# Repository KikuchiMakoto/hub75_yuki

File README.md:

# HUB75 LED Matrix Controller System

128x32 HUB75 LEDマトリックスパネルを制御する完全なシステムです。RP2040 (Raspberry Pi Pico) とPythonアプリケーションで構成されています。

## プロジェクト構成

このプロジェクトは、**Application (Python)**、**Firmware**、**KiCad PCB** の3つのコンポーネントで構成されています：

```
├── application/       # Python制御アプリケーション (PC側)
│   └── src/           # LED Matrix Controller (画像/動画/カメラ/テキスト表示)
├── firmware/          # RP2040ファームウェア (Arduino core + PIO、COBSバイナリ通信)
│   └── src/           # HUB75ドライバ (PlatformIO/Arduino)
└── kicad_pcb/         # KiCad設計データ (基板レイアウト/ライブラリ)
```

### 役割分担

- **Firmware** (`firmware/`): RP2040上で動作するC++コード。HUB75パネルの駆動、PIO/DMAによる高速出力、USB CDCによるCOBSデータ受信、RGB565からBCM変換を担当。
- **Application (Python)** (`application/`): PC上で動作するPythonコード。画像/動画読み込み、リサイズ、RGB565変換、COBSエンコード、シリアル通信を担当。
- **KiCad PCB** (`kicad_pcb/`): 回路図シンボル/フットプリント/基板レイアウトなどのハードウェア設計データを管理。

### 通信プロトコル（絶対的ルール）

すべてのファームウェア・クライアント間で、以下のプロトコルは**絶対的な不変条件**です：

- **インターフェース**: USB CDC ACM
- **ペイロード形式**: RGB565 リトルエンディアン
- **エンコーディング**: COBS (Consistent Overhead Byte Stuffing)
- **フレーム区切り**: 末尾 `0x00`
- **総画素数 / ペイロード長**: **4,096 画素（8,192 バイト）**

### 動作モードとパネル配置（64x32 パネル 2枚構成）

本システムは、64x32 HUB75 パネル 2枚の物理配置と用途に応じて、以下の **2つの公式動作モード** を備えています：

1. **NormalMode (128x32)**:
   - **配置**: 64×32 パネルを左右に連結（横長バナー配置 / デフォルト）
   - **動作**: PC 上の Python コントローラー（`application/`）から USB CDC 経由で COBS 符号化 RGB565 フレームを受信し、Core1 が高速リフレッシュ駆動。動画、画像、テキスト、時計、デモアニメーションの再生に対応。
2. **StandaloneMode (64x64)**:
   - **配置**: 64×32 パネルを上下に積層（正方形 64×64 配置。下段の2枚目パネルはリボン配線に合わせて **180度回転マッピング** されます）
   - **動作**: PC 不要の完全スタンドアローン動作。RP2040 Core0（250MHz）が ADXL335 加速度センサ（`GP26` X / `GP27` Y）を読み取り、純粋な `float` (f32) 2D-DEM 珪砂シミュレーション（Spatial Grid 近傍探索 $O(N)$ により 30+ FPS）をリアルタイム計算。Core1 が 64×64 パネルを駆動する「電子珪砂時計 / 回転ドラム」モード。起動時の突入電流を抑える省電力ブート（即時ブラックアウト）を搭載。

> **更新レート（FPS）について**: これは**緩いルール**です。目標FPSはファームウェアの実装・最適化状況次第で変化します。クライアント側はできる限りのレートで送信し、ファームウェア側が受信・描画可能なタイミングで処理します。プロトコル形式（RGB565+COBS+0x00）を守ることが最優先です。

## 特徴

- **高速・安定表示**: PIO (7.14 MHz 最適化) + DMA による高速シフト出力（内部リフレッシュレート約 350 Hz、フリッカーフリー）
- **デュアルコア設計**: Core0 で USB 受信／DEM 物理演算＋BCM 変換、Core1 で 100% パネル駆動専任（完全チラつき防止）
- **ハードウェア除算アクセラレーション**: RP2040 SIO 32-bit 除算器による DEM 物理演算の高速化（約 250 FPS）
- **過大評価描画**: 2x2 box pixel の隙間・角抜けを排除した高密度・高輝度砂粒表示
- **即時起動**: 余計な起動スプラッシュやセルフテスト待ちを全廃し、電源投入直後から即時動作
- **RGB565フォーマット**: 16ビットカラー（5-6-5ビット）による効率的な転送
- **COBSエンコーディング**: 0x00区切りのバイナリフレーム転送
- **高画質**: 6ビットBCM（64階調）+ Gamma補正（2.2）
- **最新コードベース**: 不要な低速 CPU GPIO 駆動コードを全廃し、PIO + DMA 専用に一本化

## クイックスタート

### 必要なツール

- **Firmware用**: [PlatformIO](https://platformio.org/) - RP2040へのファームウェア書き込み
- **Application (Python) 用**: [uv](https://docs.astral.sh/uv/) - Pythonパッケージマネージャー

### セットアップ手順

#### 1. Firmwareをビルド・書き込み (初回のみ)

```bash
cd firmware
pio run -t upload
```

RP2040にファームウェアが書き込まれ、HUB75パネルの駆動が可能になります。

#### 2. Application (Python) を実行 (PC側)

uvをインストール:
```bash
# macOS / Linux
curl -LsSf https://astral.sh/uv/install.sh | sh

# Windows (PowerShell)
powershell -ExecutionPolicy ByPass -c "irm https://astral.sh/uv/install.ps1 | iex"
```

アプリケーションを実行:
```bash
cd application

# デモアニメーション
uv run led-matrix --demo rainbow

# 画像表示
uv run led-matrix --image sample.png

# 2D-DEM 珪砂シミュレーション (Taichi GPU, f32)
uv run led-matrix --dem

# 2D-DEM 64x64 Pixel/Voxel マトリクス表示
uv run led-matrix --dem-matrix

# ヘルプ表示
uv run led-matrix --help
```

詳細は各ディレクトリのREADMEを参照してください:
- [Application (Python) README](application/README.md)
- [Firmware README](firmware/README.md)
- [KiCad PCB データ](kicad_pcb/)

## ハードウェア要件

- Raspberry Pi Pico (RP2040)
- HUB75 LED パネル 64x32 x 2枚
- 3軸加速度センサ ADXL335 (3.3V電源)
  - **X軸**: `GP26` (ADC0)
  - **Y軸**: `GP27` (ADC1)
  - **Z軸**: 未使用（2D DEMのため不要）
  - **VCC**: `3V3` (3.3V)
  - **GND**: `GND`
- USBケーブル
- 5V電源 (LEDパネル用)

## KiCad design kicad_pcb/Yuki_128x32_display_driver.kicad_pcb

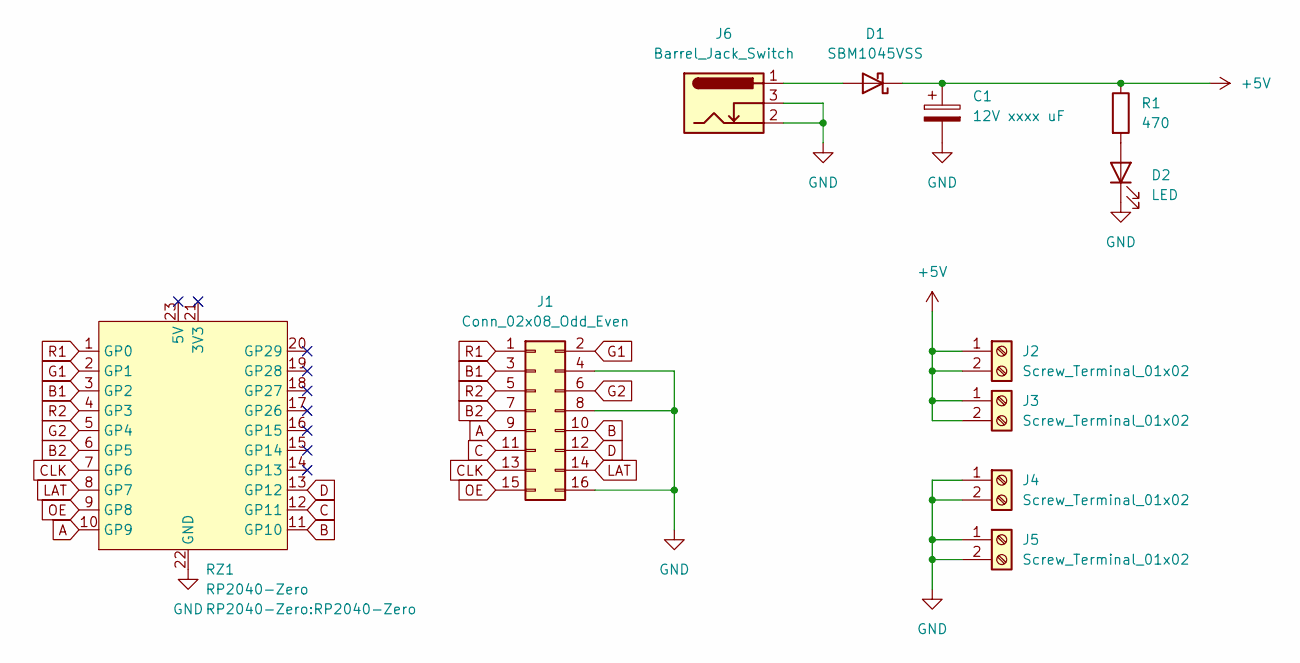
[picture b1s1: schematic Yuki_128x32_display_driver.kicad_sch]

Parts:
C1: 12V xxxx uF; CP_Radial_D13.0mm_P5.00mm
D1: SBM1045VSS; D_DO-201AD_P12.70mm_Horizontal
D2: LED; LED_D5.0mm
J1: Conn_02x08_Odd_Even; IDC-Header_2x08_P2.54mm_Vertical
J2, J3, J4, J5: Screw_Terminal_01x02; TerminalBlock_MaiXu_MX126-5.0-02P_1x02_P5.00mm
J6: Barrel_Jack_Switch; BarrelJack_Horizontal
R1: 470; R_Axial_DIN0204_L3.6mm_D1.6mm_P7.62mm_Horizontal
RZ1: RP2040-Zero

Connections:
+5V: C1.1, D1.1 (K), J2.1, J2.2, J3.1, J3.2, R1.1
A: J1.9, RZ1.10 (GP9)
B: J1.10, RZ1.11 (GP10)
B1: J1.3, RZ1.3 (GP2)
B2: J1.7, RZ1.6 (GP5)
C: J1.11, RZ1.12 (GP11)
CLK: J1.13, RZ1.7 (GP6)
D: J1.12, RZ1.13 (GP12)
G1: J1.2, RZ1.2 (GP1)
G2: J1.6, RZ1.5 (GP4)
GND: C1.2, D2.1 (K), J1.4, J1.8, J1.16, J4.1, J4.2, J5.1, J5.2, J6.2, J6.3, RZ1.22 (GND)
LAT: J1.14, RZ1.8 (GP7)
unnamed: D1.2 (A), J6.1
unnamed: D2.2 (A), R1.2
OE: J1.15, RZ1.9 (GP8)
R1: J1.1, RZ1.1 (GP0)
R2: J1.5, RZ1.4 (GP3)

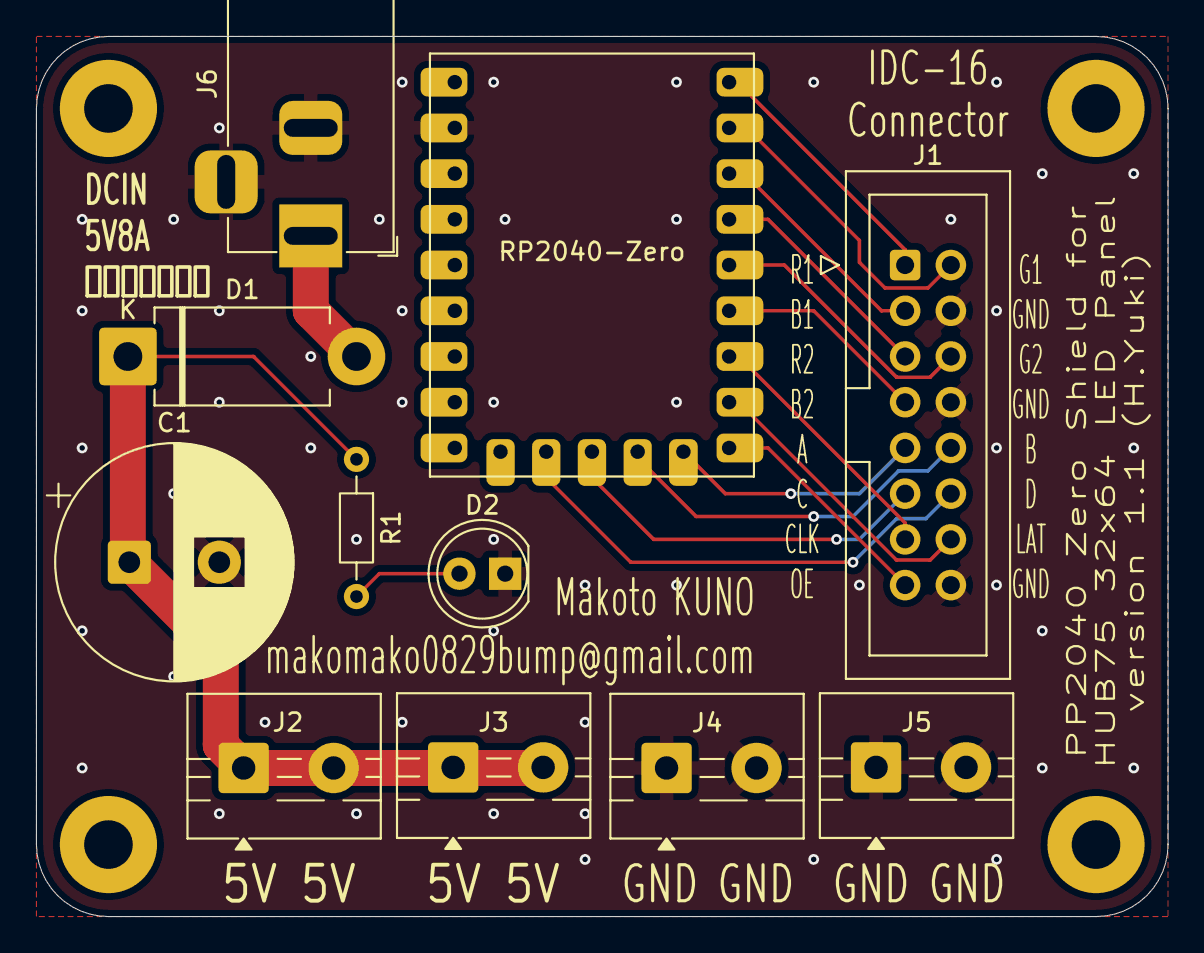
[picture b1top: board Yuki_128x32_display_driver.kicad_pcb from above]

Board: 2 copper layers, 62.9 x 48.9 mm, 11 parts (0 on the bottom side), 17 nets.

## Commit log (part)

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2025-12-16 add sources
2025-12-16 Replace PIO with CPU GPIO for HUB75 panel driving, add RGB boot screen
    - Disable PIO-based pixel shifting and use CPU GPIO directly on Core1
    - Add shift_out_pixel() function for bit-banging RGB data via GP0-5
    - Add show_boot_screen() with RGB color sweep animation at startup
    - Red, Green, Blue bands sweep across the display on power-on
2025-12-16 Fix HUB75 GPIO driving with direct register access
    - Add hardware/structs/sio.h for sio_hw register access
    - Use direct sio_hw->gpio_set/clr for fast GPIO operations
    - Mark timing-critical functions with __not_in_flash_func
    - Simplify boot screen: solid R->G->B->W colors at max brightness
    - Fix row address bit extraction with clear operator precedence
    - Increase clock pulse NOPs for reliable data latching
2025-12-16 Add PIO/GPIO mode switching via build flag
    - Add HUB75_USE_PIO define to switch between PIO and CPU GPIO modes
    - Default to PIO mode (HUB75_USE_PIO=1) for high-speed shifting
    - platformio.ini: Add two environments:
    - pico: PIO mode (default, recommended)
    - pico_gpio: CPU GPIO bit-banging mode
    - Boot screen works in both modes using direct GPIO
2025-12-16 Update READMEs to use uv as the package manager
    - application/README.md: Standardize all commands to use `uv run led-matrix`
    instead of mixed `python -m led-matrix` usage
    - Add uv installation instructions for macOS, Linux, and Windows
    - Add prerequisites section with Python version requirements
    - Update project structure documentation
    - Remove emoji icons from section headings
2025-12-16 Remove camera and text scroll features from application
    - Remove camera_input() method for webcam capture
    - Remove display_text() and scroll_text() methods
    - Remove --camera, --text, --scroll, --scroll-speed, --camera-id CLI args
    - Update docstrings and help text to reflect remaining features
    The application now focuses on image and video display only.
2025-12-16 Remove text input support from features list
2025-12-16 Move BCM conversion from Core1 to Core0 for flicker-free display
    Core1 (loop1) now only executes hub75_refresh() with no other operations.
    Frame check and BCM conversion moved to Core0 (loop0) to prevent display
    flickering caused by Core1 being occupied with non-refresh tasks.
2025-12-16 Improve video FPS with binary transfer mode
    - Add binary transfer mode to bypass Base64 encoding overhead (33% less data)
    - Add magic header (0xFF 0x00) to distinguish binary from Base64 mode
    - Add --max-fps flag to ignore video FPS limit
    - Add --no-ack flag for asynchronous frame transfer
    - Optimize serial buffer sizes for higher throughput
    - Binary mode enabled by default (use --base64 for compatibility)
2025-12-16 Remove text display and fill options from README.md
2025-12-16 Fix Core0 USB stability with comprehensive buffer overflow protection
    Addresses long-running stability issues where Core0's USB receive task
    would become unresponsive, causing TinyUSB CDC-ACM to stop and Windows
    COM port communication errors.
    Changes:
    - Add bounds checking to base64_decode() with max_output parameter
    - Implement strict offset validation in binary mode transfer
2025-12-16 Replace Base64/binary modes with COBS encoding for memory safety
    Switch to COBS (Consistent Overhead Byte Stuffing) for all data transfer
    between application and firmware. This provides better memory safety and
    clearer packet framing.
    Benefits:
    - Clear packet boundaries (0x00 delimiter)
    - Built-in framing prevents partial packet corruption
2025-12-16 Remove ACK responses for faster, simpler communication
    Remove all ACK ('K'/'E') responses from firmware and corresponding
    ACK handling from application. This eliminates unnecessary round-trip
    delays and simplifies the protocol.
    Firmware changes:
    - Remove Serial.write('K') and Serial.write('E') calls
    - Invalid packets are silently discarded
2025-12-16 Remove deprecated --max-fps and --no-ack command-line options
    These options are no longer needed:
    - --max-fps: Frame dropping now always maintains real-time playback
    - --no-ack: ACK responses were already removed in previous commits
    Simplified the video playback API by removing max_fps and wait_ack
    parameters from play_video() method.
2025-12-16 Separate application and firmware components clearly
    - Remove firmware/host/hub75_sender.py (old Python implementation)
    - Update firmware/README.md to reference application directory
    - Update root README.md to clarify separation of concerns:
    - Firmware: C++ code for RP2040 (HUB75 driver + USB communication)
    - Application: Python code for PC (image processing, video, demos)
    This change ensures a clear architectural boundary between the
2025-12-16 Update HUB75 connector pinout in README
2025-12-16 Add web application with Web Serial API support
    - Create web_application folder with TypeScript + Bun + React + Tailwind CSS
    - Implement Web Serial API communication layer
    - COBS encoding for data transmission
    - RGB565 image conversion
    - Serial device connection management
    - Add drag-and-drop support for images and videos
2025-12-16 Update README by removing license and contribution sections
    Removed license and contribution sections from README.
2025-12-17 Include ffmpeg commands in README
    Add sample ffmpeg commands for video conversion.
2025-12-17 Fix Tailwind CSS v4 configuration for web application
    Update PostCSS and CSS config to use Tailwind v4 syntax:
    - Add @tailwindcss/postcss package
    - Update postcss.config.js to use new plugin name
    - Update index.css to use @import directive
2025-12-17 Fix TypeScript configuration and type imports
    - Add DOM and DOM.Iterable to tsconfig lib for browser APIs
    - Add @types/w3c-web-serial for Web Serial API types
    - Use type-only imports for DemoType (required by verbatimModuleSyntax)
2025-12-17 Deploy web application to docs [skip ci]
2025-12-17 remove assets
2025-12-17 Fix video buffering stability for smoother playback
    Firmware:
    - Simplify frame handling to single-buffer approach
    - Process frame immediately on complete reception
    - Remove complex double-buffering flag management
    - Reference: LED_Matrix_firmware_K00798
    Application:
2025-12-17 Limit video mode maximum frame rate to 15fps
    - Add MAX_VIDEO_FPS constant (15fps) to both Python and Web applications
    - Remove transfer rate FPS checking from video playback display
    - Frame dropping is now based on video's original frame rate
    - Add sleep/interval control to maintain target FPS output
    - Update setTargetFps() to cap at 15fps maximum
2025-12-19 Add DMA-based LED panel refresh with double buffering
    Phase 1 & 2 implementation:
    - Add DMA channel for PIO FIFO data transfer
    - Implement double buffering (ping-pong) for pipelined operation
    - Prepare next row's data while current row is being transferred
    - Reduces CPU load on core1 during display refresh
    - DMA handles pixel data transfer, CPU handles control signals
2025-12-19 Fix CDC endpoint buffer size to 512 for better throughput
2025-12-19 Increase maximum video FPS from 15 to 18
2025-12-19 del github actions
2025-12-21 del docs
2025-12-21 Add ffmpeg.wasm video preprocessing and GitHub Pages deployment
    - Implement video resize using ffmpeg.wasm to convert videos to 128x32 resolution
    - Videos are preprocessed to MP4 format with 18fps limit for better OpenCV2 compatibility
    - Add VideoProcessor class to handle ffmpeg.wasm operations
    - Update App.tsx to use video preprocessing before playback
    - Add GitHub Actions workflow for automatic GitHub Pages deployment
    - Use actions/upload-pages-artifact and actions/deploy-pages for deployment
2026-02-15 Add CLAUDE.md with comprehensive codebase documentation for AI assistants
    Covers project structure, build commands for all three components
    (firmware/application/web), communication protocol details, code
    conventions, linting/testing setup, and key architectural notes.
    https://claude.ai/code/session_01CnEjKmv1HmX4y7UkmdxvTa
2026-03-22 add kicad pcb sources
2026-03-22 docs: update README and add kicad_pcb gitignore
    Agent-Logs-Url: https://github.com/KikuchiMakoto/hub75_yuki/sessions/483cf950-8b47-4fbb-86f1-b34b762b84f9
2026-03-22 fix: keep KiCad project files tracked in gitignore
    Agent-Logs-Url: https://github.com/KikuchiMakoto/hub75_yuki/sessions/483cf950-8b47-4fbb-86f1-b34b762b84f9
2026-03-22 不要なファイルを削除
2026-03-22 add pcb data
2026-03-22 update gitignore
2026-03-22 fix: improve web serial streaming resilience
2026-03-22 docs: align firmware protocol wording with COBS framing
2026-03-22 feat: add firmware_v2 pico-sdk tinyusb core
2026-03-22 chore: add firmware_v2 docs and benchmark tooling
2026-04-21 update kicad
2026-04-21 update firmware
2026-04-26 Add firmware_v3 with 9-bit native BCM, PIO/DMA optimization, and release workflow
    - Add firmware_v3: high-performance RP2040 firmware with 9-bit native
    BCM (512 levels), 5px/32bit PIO packing (93.75% FIFO efficiency),
    Core0 conversion + Core1 display architecture
    - Harden firmware_v2: remove critical_section from Core1, fix DMA
    register access, improve gamma LUT accuracy, direct DMA from
    bcm_planes without CPU copy
2026-04-26 Update deployment workflow to use only 'main' branch
    Remove 'master' branch from deployment triggers.
2026-04-26 Update release-firmware.yml to trigger on main branch push
2026-04-26 Fix firmware build issues for GitHub Actions
    - Fix gamma8 LUT element count in firmware_v2 (256 elements)
    - Add clean build step to remove stale .pio/build cache
    - Isolate PlatformIO cache per project to avoid cross-contamination
    - Use hashFiles per-project platformio.ini for cache key
2026-04-26 Add KiCad/.history and build dirs to .gitignore
    - Remove accidentally committed kicad_pcb/.history (embedded git repo)
    - Add .pio/build/, build/, cmake-build-*/ to .gitignore
    - Add kicad_pcb/.history/ to .gitignore
2026-04-26 Fix GitHub Actions: remove PlatformIO cache to prevent stale package conflicts
    - Remove ~/.platformio from cache (was causing duplicate PicoSDK library links)
    - Keep only pip cache for faster PlatformIO installation
    - Add pio system prune --force before each build
    - Clean .pio/build and ~/.platformio/.cache explicitly
2026-04-26 Rename application/ to application_py/ and web_application/ to application_web/
    Update all references in workflows, READMEs, and AGENTS.md to match
    the new directory names. No functional changes.
